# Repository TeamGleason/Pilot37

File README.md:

# Pilot37
A platform to drive FPV Cars &amp; Drones from a Microsoft Surface using Eye Control

## Hardware & Software Requirements
To complete this project, you will need:
 * Tobii Bundle Version (???) and Drivers (???)
 * Tobii PCEye Mini sensor
 * Windows Surface or PC running Windows 10 Creators Update, Build Version 15063 or higher
 * USB 3.0 Hub
 * USB 5.8GHz Video Receiver (https://www.aliexpress.com/item/5-8G-FPV-Receiver-UVC-Video-Downlink-OTG-VR-Android-Phone-PC-Micro-USB-AMP-Pix/32723892492.html)
 * FOXEER TM600 FPV 5.8GHz 40CH 600mW Transmitter 
 * RunCam Eagle2 FPV Camera (http://shop.runcam.com/runcam-eagle-2/)
 * Traxxas Stampede RC Car
 * RedBear BLE Nano 2 (using Nordic nRF52832 chip)

## Set-Up
To get this project rolling, you will need to acquire one of the custom PCB breakout boards we designed to enable the Nano 2 to control the motors of the RC car/drone:

You will need to solder the Nano 2 to this PCB, as well as some headers to expose the various PWM and GPIO ports of the board. With this done, the PCB can be placed onto the RC car/drone as follows (NOTE: This PCB is a copper-plated prototype made on an OtherMill):

Once the PCB is ready and the headers are soldered, you can plug in your various servo motors and FPV transmitter according to the BLE specifications as to which pins output which signals.

To setup the remote controller portion of this project, you must first walk through the instructions given to you by the Tobii installation software to properly set up your eye-tracker sensor. Once finished, simply plug in your USB hub and attach both the PCEye Mini sensor and the USB 5.8GHz Video Receiver, and you are good to go. Now all you have to do is turn on the RC car/drone and launch the application.

## Things to Watch Out For
Sometimes the BLE connection can exhibit buggy behavior at the boundaries of the radio's range. Most of the time, bringing the BLE device back into the range of the Windows Surace or PC will solve all problems, but sometimes turning the device ON and OFF again will ensure proper behavior. If bugs persist, restart the application.

## Developers Note
For more robust and secure applications, consider enabling a Heartbeat and/or Watchdog timer to detect when the system is non-responsive. The current code does have a Heartbeat system in place (currently commented out), but it has not been tested and will undoubtedly be buggy.
There are only 2 files that make up this application, SettingsPage.xaml.cs and MainPage.xaml.cs. A single Gaze Pointer is created, which traverses both pages upon in-app frame navigation, although this should be changed in future iterations to match the standard programming pattern of other Eye Gaze applications (ie, on navigation to any new page, a new Gaze Pointer object should be created, then killed when navigating to a new page).

### Main Page
The MainPage is where the user will actually drive the RC car/drone. The background of this page displays the incoming FPV video stream from the RC car/drone, with semi-opaque driving buttons overlayed on top. Toggling the "Pause" button allows users to disable all functionality of the drive buttons until the "Pause" button is toggled once more. Clicking the settings button (button with gear icon) navigates the app to the Settings Page. To drive the RC car in reverse, users MUST select the reverse button, then select the stop button, then select the reverse button once more. A BLE indicator at the bottom-left of the screen displays the connection status of the BLE device.

### Settings Page
The main purpose of this page is to allow users to configure their own customized settings that work with their specific RC car. Users can save these customized settings so that they persist every time you re-launch the application. Users can also enable "personality actions" from the Settings page, which consists of a button to automatically do 'Donuts' and a button to 'Wave' at friends. Lastly, users can terminate the application from this Settings page.
Note: The Settings Page is DISABLED when the BLE device is DISCONNECTED from the Windows Surface or PC to avoid connection issues when the user navigates to the Settings Page. In this scenario, the Settings Button is converted into an "EXIT" button, which will terminate the app.

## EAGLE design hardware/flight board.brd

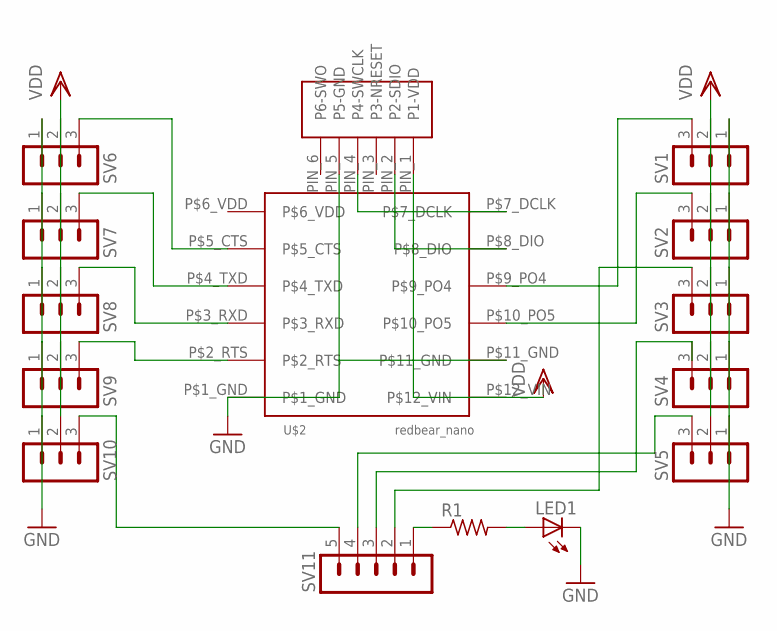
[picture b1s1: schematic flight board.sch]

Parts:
LED1: LED_ESML0603; LED_SML0603
R1: R-US_R0603; R0603
SV1, SV2, SV3, SV4, SV5, SV6, SV7, SV8, SV9, SV10: MA03-1
SV11: MA05-1
U$1: TAG_CONNCET; TAG_CONNECT
U$2: REDBEAR_NANO

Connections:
GND: LED1.C, SV1.1, SV2.1, SV3.1, SV4.1, SV5.1, SV6.1, SV7.1, SV8.1, SV9.1, SV10.1, U$1.PIN_5 (P5-GND), U$2.P$1_GND, U$2.P$11_GND
unnamed: SV6.3, U$2.P$5_CTS
unnamed: SV7.3, U$2.P$4_TXD
unnamed: U$1.PIN_4 (P4-SWCLK), U$2.P$7_DCLK
unnamed: U$1.PIN_2 (P2-SDIO), U$2.P$8_DIO
unnamed: SV8.3, U$2.P$3_RXD
unnamed: SV9.3, U$2.P$2_RTS
unnamed: SV10.3, SV11.5
unnamed: R1.1, SV11.1
unnamed: SV1.3, U$2.P$9_PO4
unnamed: SV2.3, U$2.P$10_PO5
unnamed: SV5.3, SV11.4
unnamed: SV4.3, SV11.3
unnamed: LED1.A, R1.2
unnamed: SV3.3, SV11.2
VDD: SV1.2, SV2.2, SV3.2, SV4.2, SV5.2, SV6.2, SV7.2, SV8.2, SV9.2, SV10.2, U$1.PIN_1 (P1-VDD), U$2.P$12_VIN

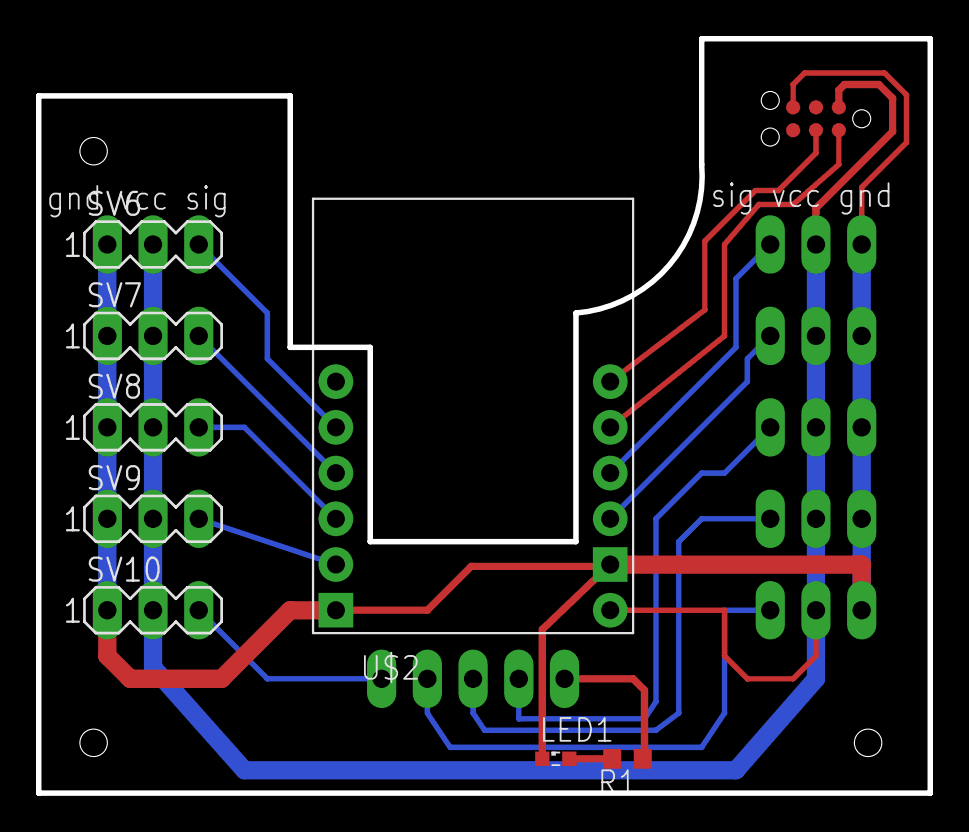
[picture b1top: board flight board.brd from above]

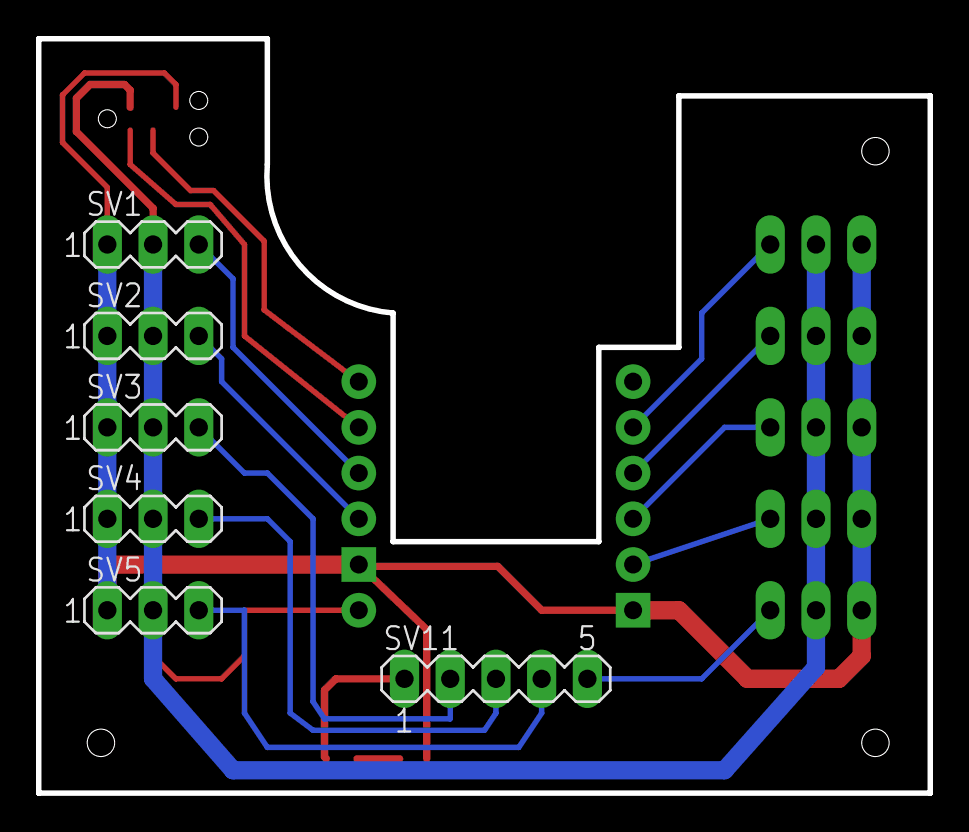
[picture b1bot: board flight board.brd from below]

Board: 2 copper layers, 49.5 x 41.9 mm, 15 parts (6 on the bottom side), 16 nets.

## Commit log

2017-07-03 gitignore
2017-07-04 tools
2017-07-04 baseline sample
2017-07-04 remove dead code
2017-07-05 config file
2017-07-05 move to receiver service
2017-07-07 device id characteristic building blocks for gpio and pwm
2017-07-07 lots of pwm setup
2017-07-07 writable characteristics (heartbeat, pwm, gpio) (no real wiring but lots of plumbing)
2017-07-10 simplistic failsafe
2017-07-10 update comment
2017-07-11 build for proto hw gpio, pwm turned off so just characteristics enumeration guids/characteristics have not yet been made custom
2017-07-12 remote control of a gpio + failsafe Issue: control can still take place with device in failsafe state.
2017-07-13 Integrated, functional structure for Pilot37
    TODO: Make two separate projects for Pilot37_RCCar and Pilot37_Drone. Each of these projects require different GUIs, commands, etc to control the device. Small example --> Pilot37_RCCar needs 2 FPV s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
    Discovery of and communication with nRF52832 BLE Heart Rate Monitor devices works.
    FPV video stream reception and display works with external webcam devices.
    Basic GUI is set up and ready to start making writes to our BLE device.
2017-07-17 cleanup w/o fixes
2017-07-17 pwm fixes
2017-07-17 validate bluetooth write without response characteristics against the computed length
2017-07-17 appears to work
2017-07-17 failsafe 400ms tested at 20000ms manually
    can be disabled w/recompile
2017-07-18 our own uuid/service/characteristics
2017-07-19 latency fixes not very tight heartbeat requirement
2017-07-20 Add OSX setup script
2017-07-20 much tighter connection interval, param update frequency, connection timeout failsafe off
2017-07-20 Add printf debugging
2017-07-20 Move to Segger_rtt_printf for reliable traceline debugging, printf() was not consistently working
2017-07-21 Turn on failsafe on ble disconnect, turn up ble logging, rename firmware
2017-07-21 Additional debug message tuning
2017-07-21 Pilot 37 RCCar Application
    Todos:
    + Enable Gaze Events and configure the delay timers for proper Eye Gaze control (Need EyesOff for the GazeInput library)
    + Fix UnhandledException Handling
    + Test the user experience and calibrate the controls
    * GOAL: Settings window for eye gaze enabled parameter configuration // 2 Cameras
2017-07-24 Change logging which seemed to help boot process
2017-07-25 add infinite slow advertising. evaluate reliability of connect
2017-07-26 Checking in working code from Demo with Steve Gleason
2017-07-27 BLE is fully functional and can now connect and disconnect in same session
2017-07-27 Basic structure for the new GUI, and Settings Window on its way
2017-07-28 New GUI implemented. Speed controls need fixing. Make a Settings window that is EyeGaze enabled and doesnt mess with BLE
2017-07-29 Settings Window is now EyeGaze enabled, and the GazeInput bug for this has been fixed. Need to disconnect from BLE when exiting the app, fix the drive speeds, make adjustable settings, handle when BL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
2017-07-29 hardware
    this is all the relevant files for the control board for the RC car
2017-08-07 system diagram of hardware
2017-08-07 Unzip hardware files
2017-08-10 Fully functional Settings Page, with added UI indication for BLE connection status and new Logo Assets. Need to add Personality Actions and also test the newly working UnhandledExceptions.
2017-08-10 Optimized internal parameters for Slow Speed variable range. Added comments of all exceptions encoutnered while testing BLE connection. Need to finish implementation of UnhandledException, and invest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
2017-08-11 Unhandled Exception handler basically works. Getting help from BLE team regarding Filtering for UUIDs and Disconnecting. Need to look into creating a new BLE Advertisement Watcher each time the MainP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
2017-08-11 Unhandled Exceptions works. Frame navigation with BLE connectivity works. Working with BLE Team to fix Filtering by UUID and Programmatic Disconnect from BLE. Need to test everything on a new target 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
2017-08-15 BLE has no more bugs. Also made edits to XAML files for dynamic resizing on different platforms
2017-08-16 Final Version of the application. Now all that is left is getting the Tobii Drivers to cooperate on the new Surfaces
2017-08-16 Final App fully working. Still fixing the Tobbi HID driver bug
2017-08-18 Reorganized the code layout for easier use. Added comments for more detail
2017-08-19 Added photos for documentation
2017-08-19 Rotated image
2017-08-19 Resized photo
2017-12-07 Add files via upload
    v5 board
